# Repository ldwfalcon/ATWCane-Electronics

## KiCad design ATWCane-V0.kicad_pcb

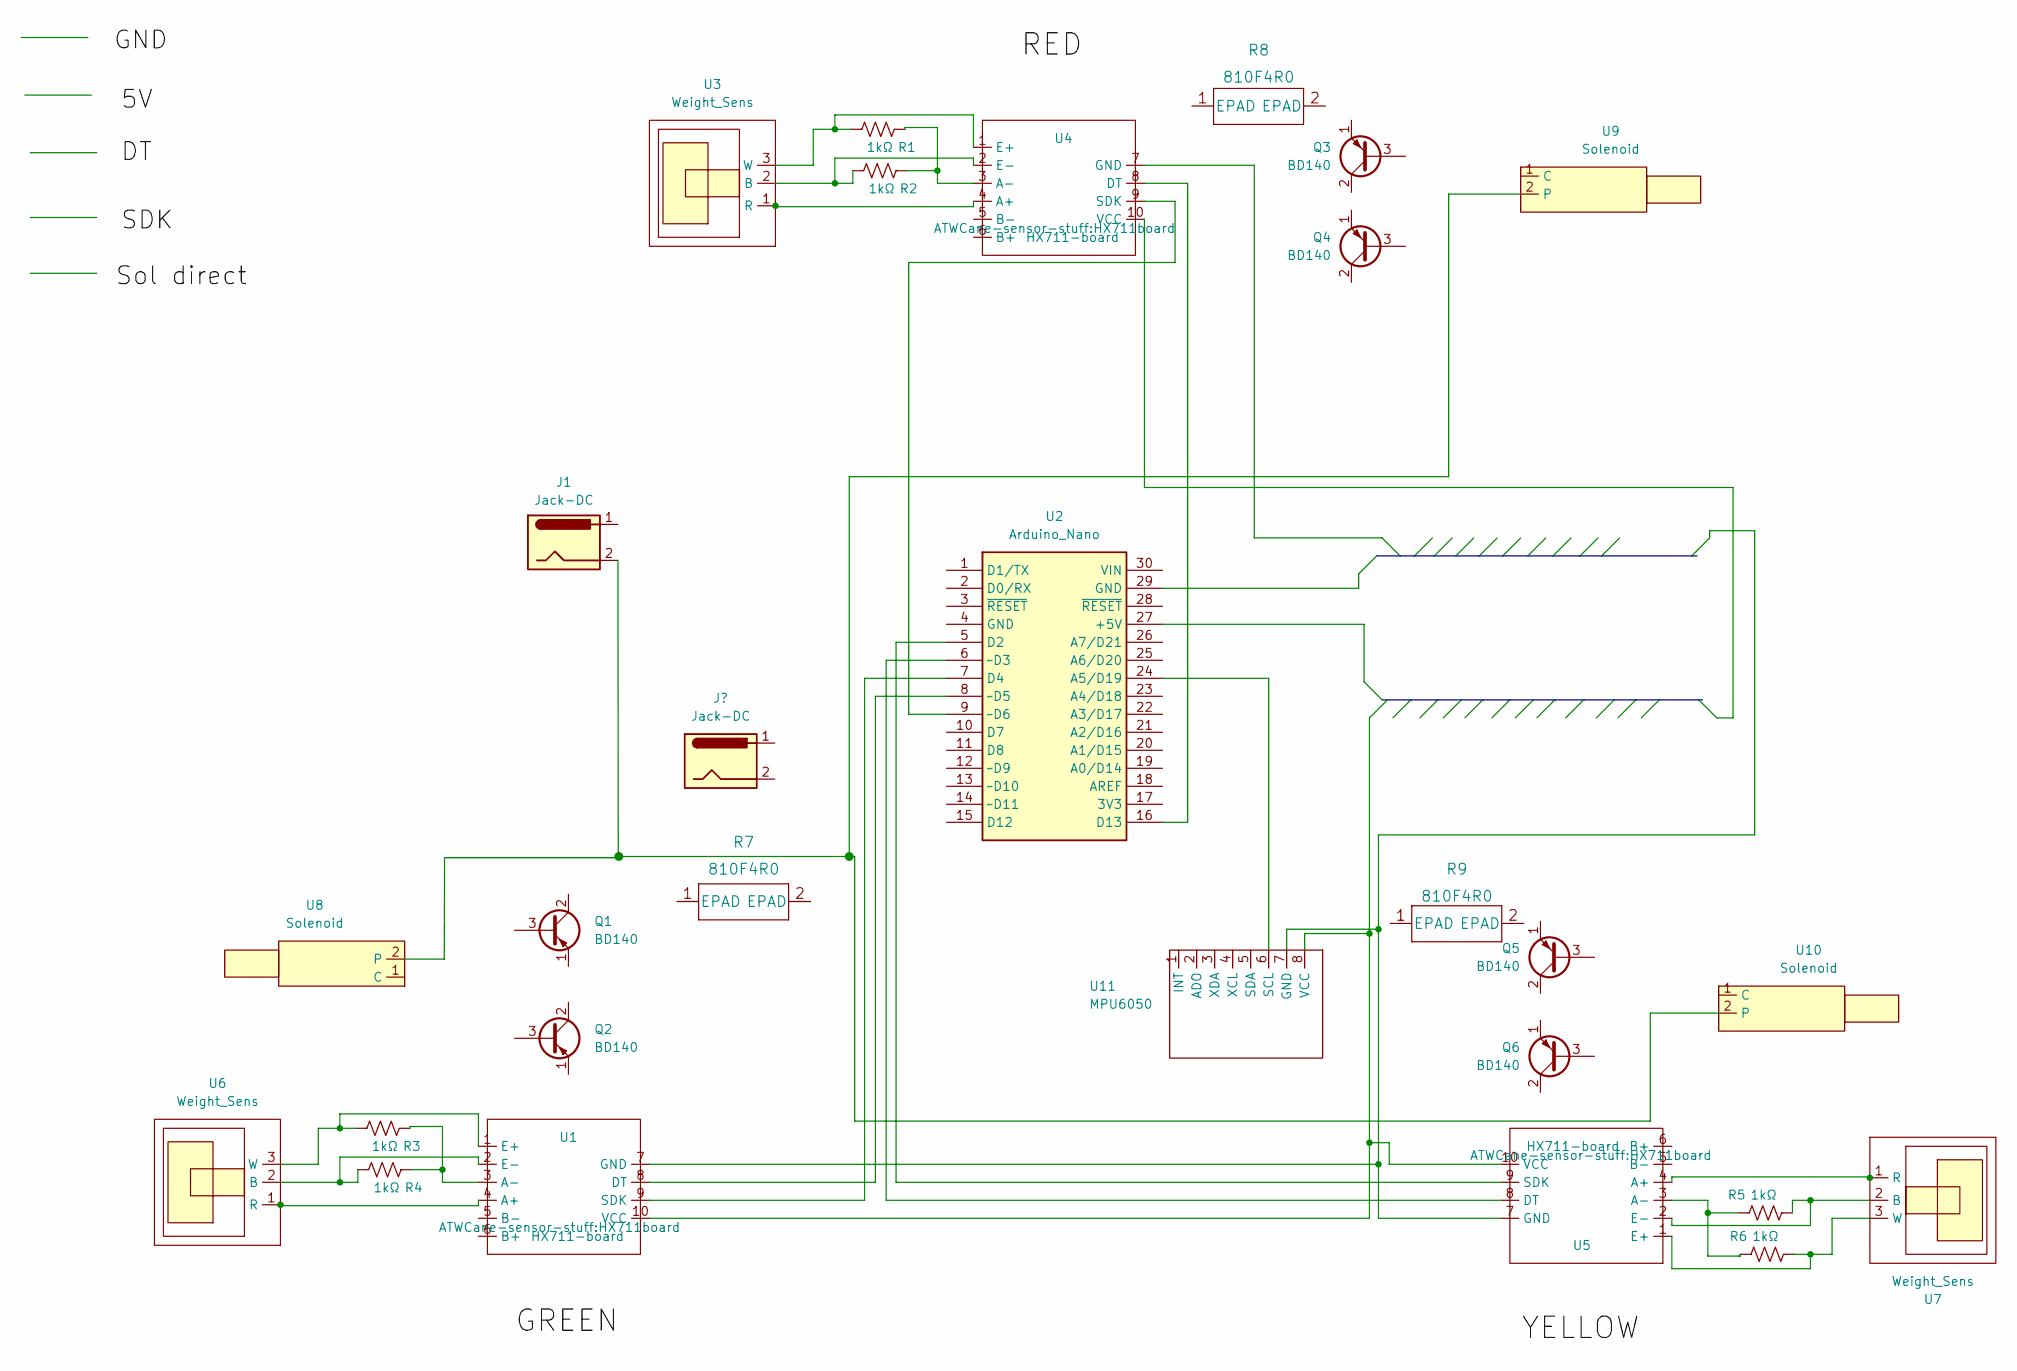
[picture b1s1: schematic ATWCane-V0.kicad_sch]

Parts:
J1: Jack-DC; BarrelJack_Horizontal
Q1, Q2, Q3, Q4, Q5, Q6: BD140; TO-220-3_VerticalHEAT
R1, R2, R3, R4, R5, R6: 1kΩ; R_Axial_DIN0207_L6.3mm_D2.5mm_P2.54mm_Vertical
R7, R8, R9: 810F4R0
U1, U4, U5: HX711-board; HX711board
U2: Arduino_Nano
U3, U6, U7: Weight_Sens; PinHeader_1x03_P2.54mm_Vertical
U8, U9, U10: Solenoid
U11: MPU6050

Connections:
unnamed: J1.2, U8.2
unnamed: R1.1, U3.3 (W), U4.1 (E+)
unnamed: R1.2, R2.2, U4.3 (A-)
unnamed: R2.1, U3.2 (B), U4.2 (E-)
unnamed: R3.1, U1.1 (E+), U6.3 (W)
unnamed: R3.2, R4.2, U1.3 (A-)
unnamed: R4.1, U1.2 (E-), U6.2 (B)
unnamed: R5.1, U5.2 (E-), U7.2 (B)
unnamed: R5.2, R6.2, U5.3 (A-)
unnamed: R6.1, U5.1 (E+), U7.3 (W)
unnamed: U1.4 (A+), U6.1 (R)
unnamed: U1.7 (GND), U5.7 (GND), U11.7 (GND)
unnamed: U1.8 (DT), U2.8 (~D5)
unnamed: U1.9 (SDK), U2.7 (D4)
unnamed: U1.10 (VCC), U5.10 (VCC), U11.8 (VCC)
unnamed: U2.5 (D2), U5.9 (SDK)
unnamed: U2.6 (~D3), U5.8 (DT)
unnamed: U2.9 (~D6), U4.9 (SDK)
unnamed: U2.16 (D13), U4.8 (DT)
unnamed: U5.4 (A+), U7.1 (R)
unnamed: U9.2, U10.2
unnamed: U2.24 (A5/D19), U11.6 (SCL)

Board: 2 copper layers, 28 parts (0 on the bottom side), 22 nets, no tracks yet.

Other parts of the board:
J2: Jack-DC; Board outline V1

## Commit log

2022-04-19 Create fp-lib-table
2022-04-19 Create sym-lib-table
2022-04-19 Create ATWCane-V0.kicad_sch-bak
2022-04-19 Create fp-info-cache
2022-04-19 Create LICENSE
2022-04-20 Update fp-info-cache
2022-04-20 Create #auto_saved_files#

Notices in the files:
parts and their libraries:
Copyright 2021 Accelerated Designs. All rights reserved.
